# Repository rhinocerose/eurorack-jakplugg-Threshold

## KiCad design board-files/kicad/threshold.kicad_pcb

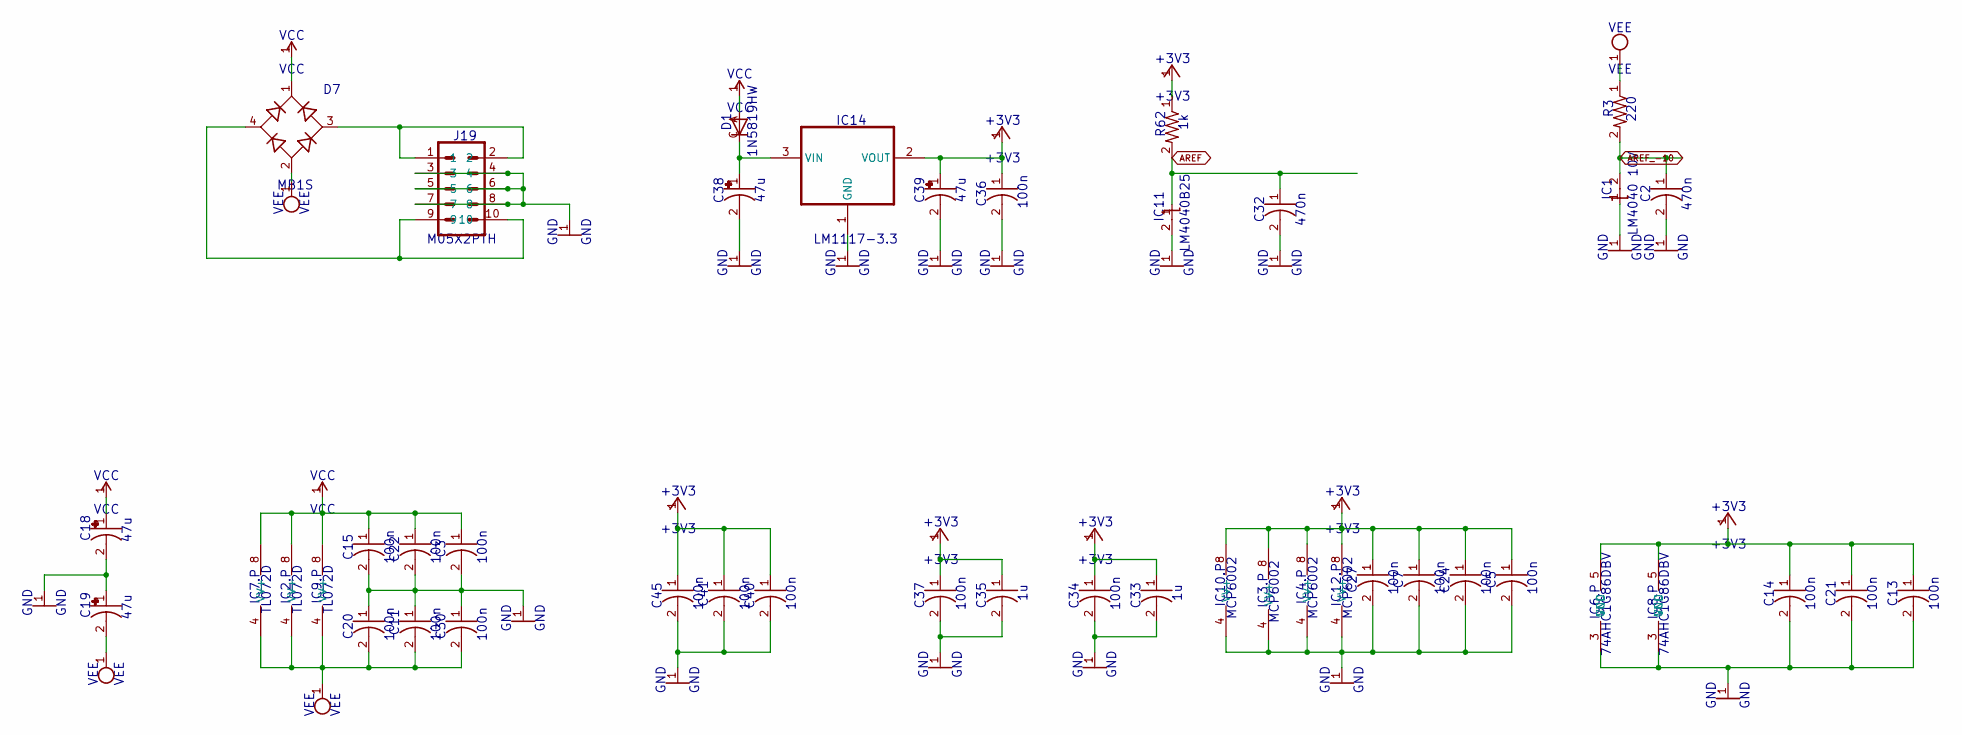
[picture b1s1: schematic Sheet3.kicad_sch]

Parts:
C2, C32: 470n; CAP_0603
C3, C5, C7, C11, C13, C14, C15, C20, C21, C22, C24, C27, C30, C34, C36, C37, C40, C41, C45: 100n; CAP_0603
C18, C19, C38, C39: 47u; CAPAE-5.3X5.3H7
C33, C35: 1u; CAP_0603
D1: 1N5819HW; SOD123
D7: MB1S; SOP-4_6.5X2.54
IC1: LM4040 10V; SOT23
IC2, IC7, IC9: TL072D; SO08_23
IC3, IC4, IC10, IC12: MCP6002; SO08_23
IC6, IC8: 74AHC1G86DBV; SOT23-5
IC11: LM4040B25; SOT23
IC14: LM1117-3.3; SOT223
J19: M05X2PTH; AVR_ICSP
R3: 220; RES_0603
R62: 1k; RES_0603

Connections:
+3V3: C5.1, C7.1, C13.1, C14.1, C21.1, C24.1, C27.1, C33.1, C34.1, C35.1, C36.1, C37.1, C39.1 (+), C40.1, C41.1, C45.1, IC3.8 (V+), IC4.8 (V+), IC6.5 (VCC), IC8.5 (VCC), IC10.8 (V+), IC12.8 (V+), IC14.2 (VOUT), R62.1; also elsewhere on the board
AREF: C32.1, IC11.1 (C), R62.2; also elsewhere on the board
AREF_-10: C2.1, IC1.2 (A), R3.2; also elsewhere on the board
GND: C2.2, C3.2, C5.2, C7.2, C11.1, C13.2, C14.2, C15.2, C18.2 (-), C19.1 (+), C20.1, C21.2, C22.2, C24.2, C27.2, C30.1, C32.2, C33.2, C34.2, C35.2, C36.2, C37.2, C38.2 (-), C39.2 (-), C40.2, C41.2, C45.2, IC1.1 (C), IC3.4 (V-), IC4.4 (V-), IC6.3 (GND), IC8.3 (GND), IC10.4 (V-), IC11.2 (A), IC12.4 (V-), IC14.1 (GND), J19.3, J19.4, J19.5, J19.6, J19.7, J19.8; also elsewhere on the board
unnamed: C38.1 (+), D1.C, IC14.3 (VIN)
Net_101: D7.3 (AC2), J19.1, J19.2
Net_139: D7.4 (AC1), J19.9, J19.10
VCC: C3.1, C15.1, C18.1 (+), C22.1, D1.A, D7.1 (+), IC2.8 (V+), IC7.8 (V+), IC9.8 (V+); also elsewhere on the board
VEE: C11.2, C19.2 (-), C20.2, C30.2, D7.2 (-), IC2.4 (V-), IC7.4 (V-), IC9.4 (V-), R3.1; also elsewhere on the board

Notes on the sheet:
100n
VEE
VCC
IC8.P
IC3.P
C19
GND
C35
C20
IC12.P
IC11
C22
+3V3
C21
C34
220
IC1
47u
C32
C11
C41
C24
C30
C15
LM1117-3.3
470n
1N5819HW
IC2.P
LM4040 10V
J19
LM4040B25
MCP6002
IC7.P
M05X2PTH
R62
TL072D
C40
C39
IC4.P
C14

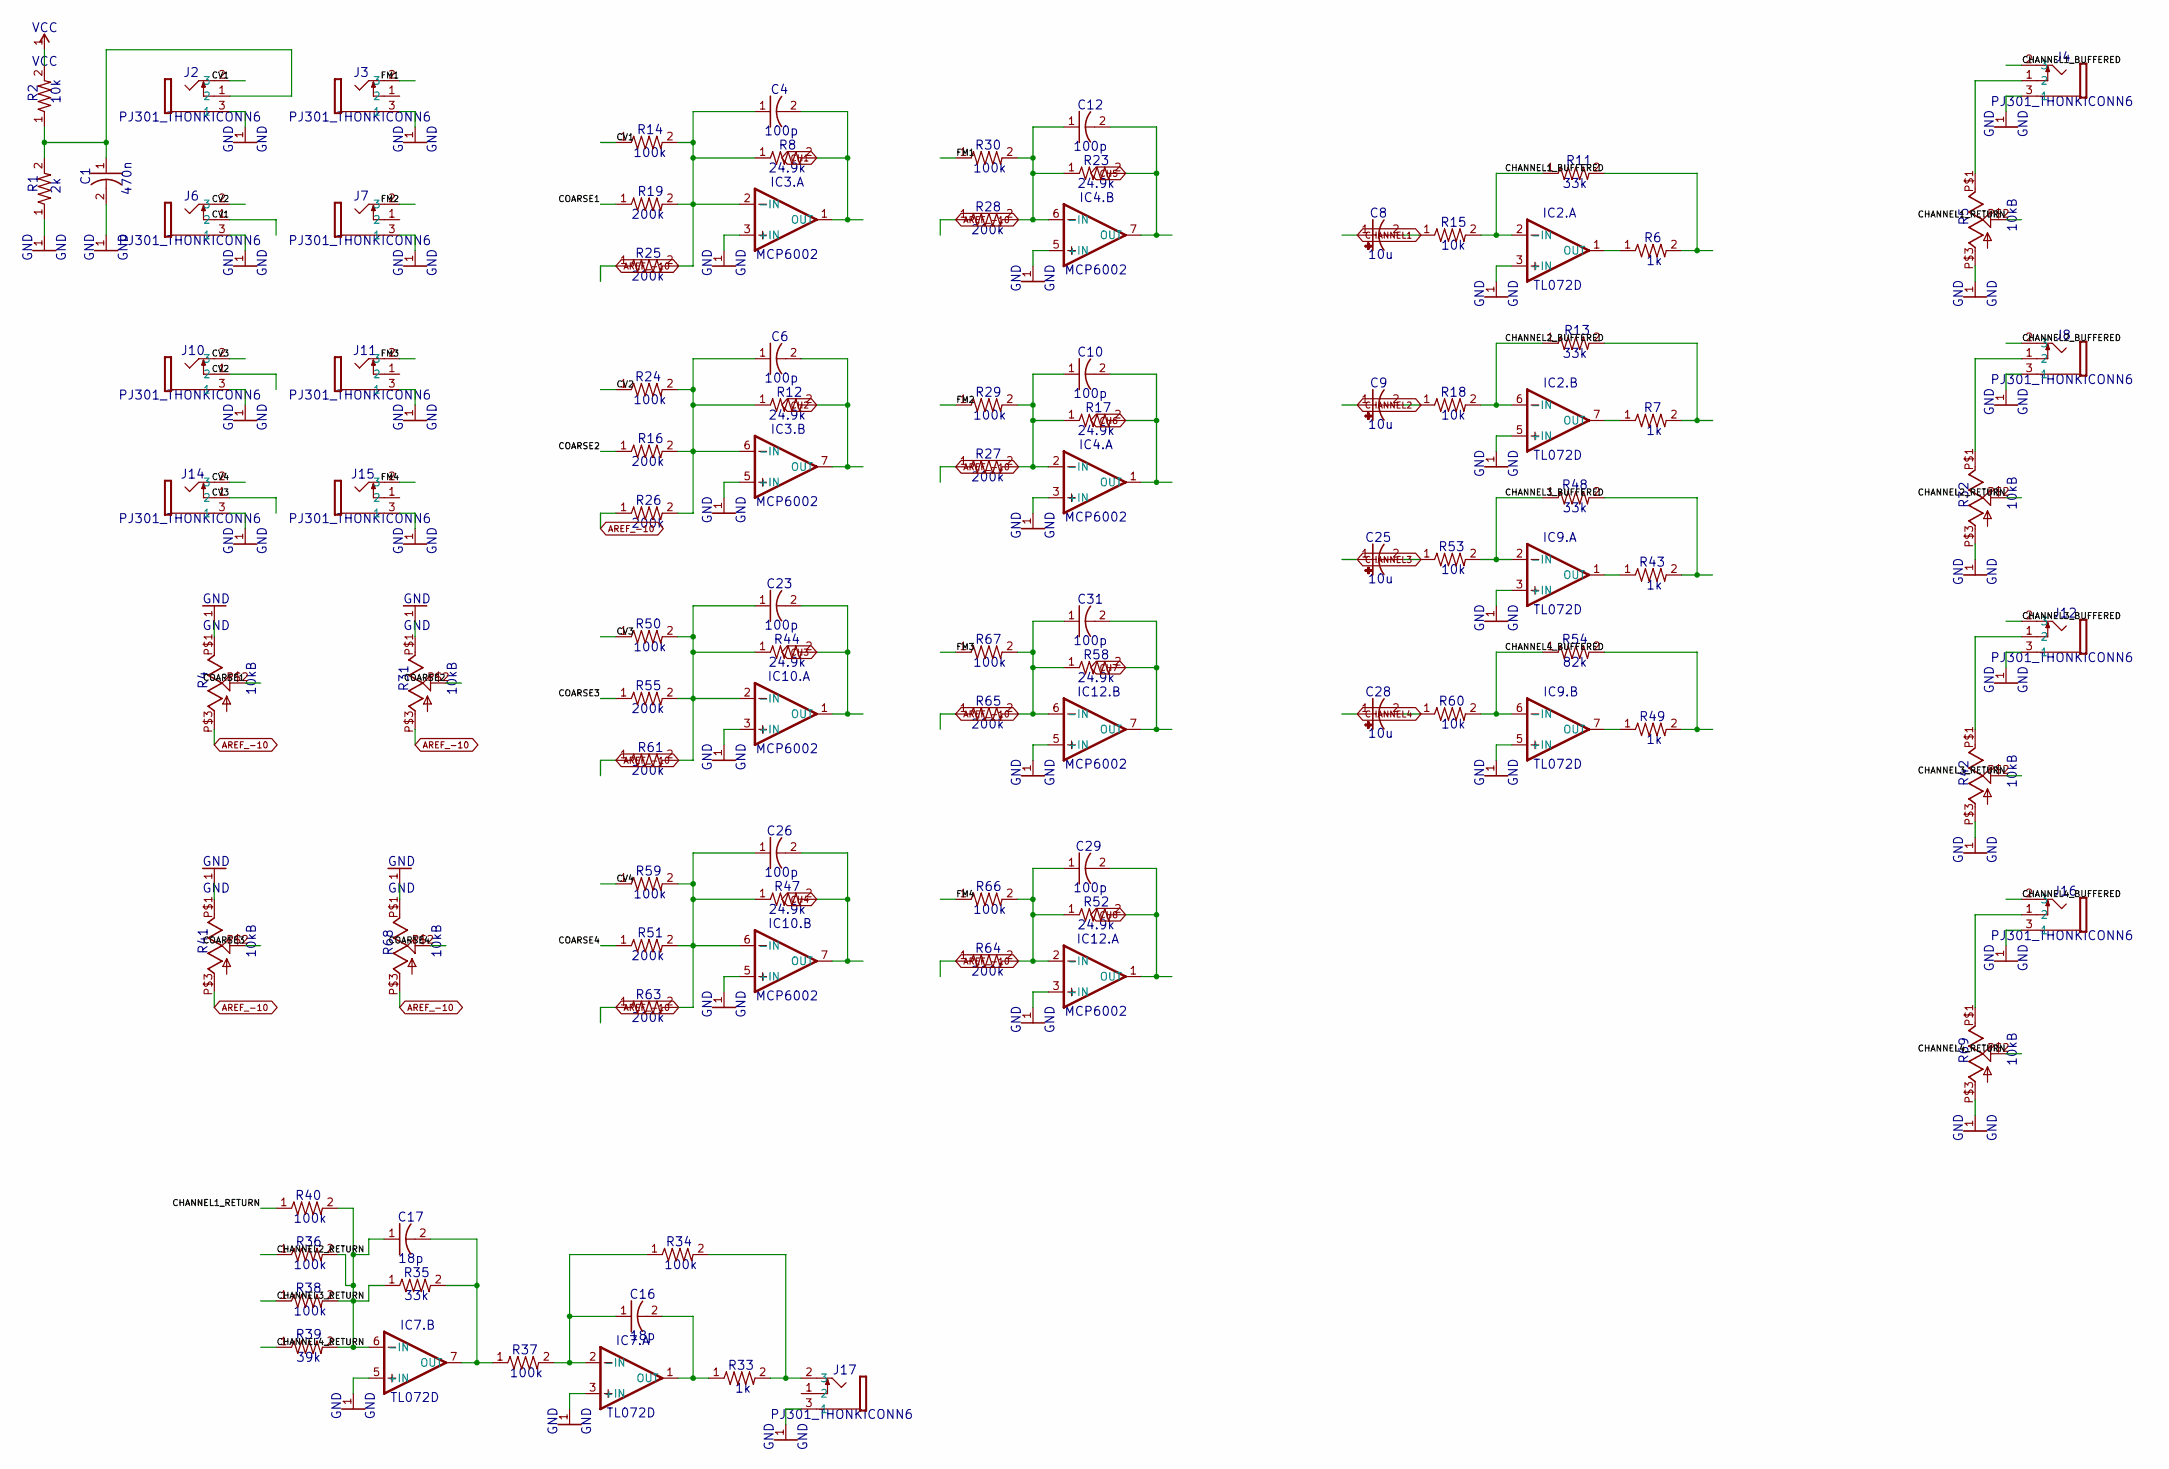
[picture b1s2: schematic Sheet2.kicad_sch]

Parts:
C1: 470n; CAP_0603
C4, C6, C10, C12, C23, C26, C29, C31: 100p; CAP_0603
C8, C9, C25, C28: 10u; CAP_1206
C16, C17: 18p; CAP_0603
IC2, IC7, IC9: TL072D; SO08_23
IC3, IC4, IC10, IC12: MCP6002; SO08_23
J2, J3, J4, J6, J7, J8, J10, J11, J12, J14, J15, J16, J17: PJ301_THONKICONN6; THONKICONN
R1: 2k; RES_0603
R2, R15, R18, R53, R60: 10k; RES_0603
R4, R5, R31, R32, R41, R42, R68, R69: 10kB; ALPS_POT_VERTICAL_PS
R6, R7, R33, R43, R49: 1k; RES_0603
R8, R12, R17, R23, R44, R47, R52, R58: 24.9k; RES_0603
R11, R13, R35, R48: 33k; RES_0603
R14, R24, R29, R30, R34, R36, R37, R38, R40, R50, R59, R66, R67: 100k; RES_0603
R16, R19, R25, R26, R27, R28, R51, R55, R61, R63, R64, R65: 200k; RES_0603
R39: 39k; RES_0603
R54: 82k; RES_0603

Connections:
AREF_-10: R4.P$3 (A), R25.1, R26.1, R27.1, R28.1, R31.P$3 (A), R41.P$3 (A), R61.1, R63.1, R64.1, R65.1, R68.P$3 (A); also elsewhere on the board
CH1: C4.2, IC3.1 (OUT), R8.2; also elsewhere on the board
CH2: C6.2, IC3.7 (OUT), R12.2; also elsewhere on the board
CH3: C23.2, IC10.1 (OUT), R44.2; also elsewhere on the board
CH4: C26.2, IC10.7 (OUT), R47.2; also elsewhere on the board
CH5: C12.2, IC4.7 (OUT), R23.2; also elsewhere on the board
CH6: C10.2, IC4.1 (OUT), R17.2; also elsewhere on the board
CH7: C31.2, IC12.7 (OUT), R58.2; also elsewhere on the board
CH8: C29.2, IC12.1 (OUT), R52.2; also elsewhere on the board
CHANNEL1: C8.1 (+); also elsewhere on the board
CHANNEL1_BUFFERED: J4.2 (3), R6.2, R11.2
CHANNEL1_RETURN: R5.P$2 (S), R40.1
CHANNEL2: C9.1 (+); also elsewhere on the board
CHANNEL2_BUFFERED: J8.2 (3), R7.2, R13.2
CHANNEL2_RETURN: R32.P$2 (S), R36.1
CHANNEL3: C25.1 (+); also elsewhere on the board
CHANNEL3_BUFFERED: J12.2 (3), R43.2, R48.2
CHANNEL3_RETURN: R38.1, R42.P$2 (S)
CHANNEL4: C28.1 (+); also elsewhere on the board
CHANNEL4_BUFFERED: J16.2 (3), R49.2, R54.2
CHANNEL4_RETURN: R39.1, R69.P$2 (S)
COARSE1: R4.P$2 (S), R19.1
COARSE2: R16.1, R31.P$2 (S)
COARSE3: R41.P$2 (S), R55.1
COARSE4: R51.1, R68.P$2 (S)
CV1: J2.2 (3), J6.1 (2), R14.1
CV2: J6.2 (3), J10.1 (2), R24.1
CV3: J10.2 (3), J14.1 (2), R50.1
CV4: J14.2 (3), R59.1
FM1: J3.2 (3), R30.1
FM2: J7.2 (3), R29.1
FM3: J11.2 (3), R67.1
FM4: J15.2 (3), R66.1
GND: C1.2, IC2.3 (+IN), IC2.5 (+IN), IC3.3 (+IN), IC3.5 (+IN), IC4.3 (+IN), IC4.5 (+IN), IC7.3 (+IN), IC7.5 (+IN), IC9.3 (+IN), IC9.5 (+IN), IC10.3 (+IN), IC10.5 (+IN), IC12.3 (+IN), IC12.5 (+IN), J2.3 (1), J3.3 (1), J4.3 (1), J6.3 (1), J7.3 (1), J8.3 (1), J10.3 (1), J11.3 (1), J12.3 (1), J14.3 (1), J15.3 (1), J16.3 (1), J17.3 (1), R1.1, R4.P$1 (E), R4.P$4, R4.P$5, R5.P$3 (A), R5.P$4, R5.P$5, R31.P$1 (E), R31.P$4, R31.P$5, R32.P$3 (A), R32.P$4, R32.P$5, R41.P$1 (E), R41.P$4, R41.P$5, R42.P$3 (A), R42.P$4, R42.P$5, R68.P$1 (E), R68.P$4, R68.P$5, R69.P$3 (A), R69.P$4, R69.P$5; also elsewhere on the board
MIX: J17.2 (3), R33.2, R34.2
unnamed: J8.1 (2), R32.P$1 (E)
unnamed: C23.1, IC10.2 (-IN), R44.1, R50.2, R55.2, R61.2
unnamed: C10.1, IC4.2 (-IN), R17.1, R27.2, R29.2
unnamed: C26.1, IC10.6 (-IN), R47.1, R51.2, R59.2, R63.2
unnamed: C31.1, IC12.6 (-IN), R58.1, R65.2, R67.2
unnamed: C29.1, IC12.2 (-IN), R52.1, R64.2, R66.2
unnamed: C8.2 (-), R15.1
unnamed: IC2.2 (-IN), R11.1, R15.2
unnamed: IC2.1 (OUT), R6.1
unnamed: C9.2 (-), R18.1
unnamed: IC2.6 (-IN), R13.1, R18.2
unnamed: IC2.7 (OUT), R7.1
unnamed: C25.2 (-), R53.1
unnamed: C12.1, IC4.6 (-IN), R23.1, R28.2, R30.2
unnamed: IC9.2 (-IN), R48.1, R53.2
unnamed: IC9.1 (OUT), R43.1
unnamed: C28.2 (-), R60.1
unnamed: IC9.6 (-IN), R54.1, R60.2
unnamed: IC9.7 (OUT), R49.1
unnamed: C17.1, IC7.6 (-IN), R35.1, R36.2, R38.2, R39.2, R40.2
unnamed: C16.1, IC7.2 (-IN), R34.1, R37.2
unnamed: C16.2, IC7.1 (OUT), R33.1
unnamed: J4.1 (2), R5.P$1 (E)
unnamed: C17.2, IC7.7 (OUT), R35.2, R37.1
unnamed: J12.1 (2), R42.P$1 (E)
unnamed: J16.1 (2), R69.P$1 (E)
unnamed: C6.1, IC3.6 (-IN), R12.1, R16.2, R24.2, R26.2
unnamed: C1.1, J2.1 (2), R1.2, R2.1
unnamed: C4.1, IC3.2 (-IN), R8.1, R14.2, R19.2, R25.2
VCC: R2.2; also elsewhere on the board

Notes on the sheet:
GND
PJ301_THONKICONN6
R50
TL072D
100k
R39
24.9k
100p
R69
R24
R48
R38
J15
J10
200k
470n
R63
R13
R43
R61
R52
10k
10u
MCP6002
R11
33k
C26
10kB
R28
R31
J11
R66
R65
R12
R49
IC7.B
IC2.B
R37
J17
IC12.B

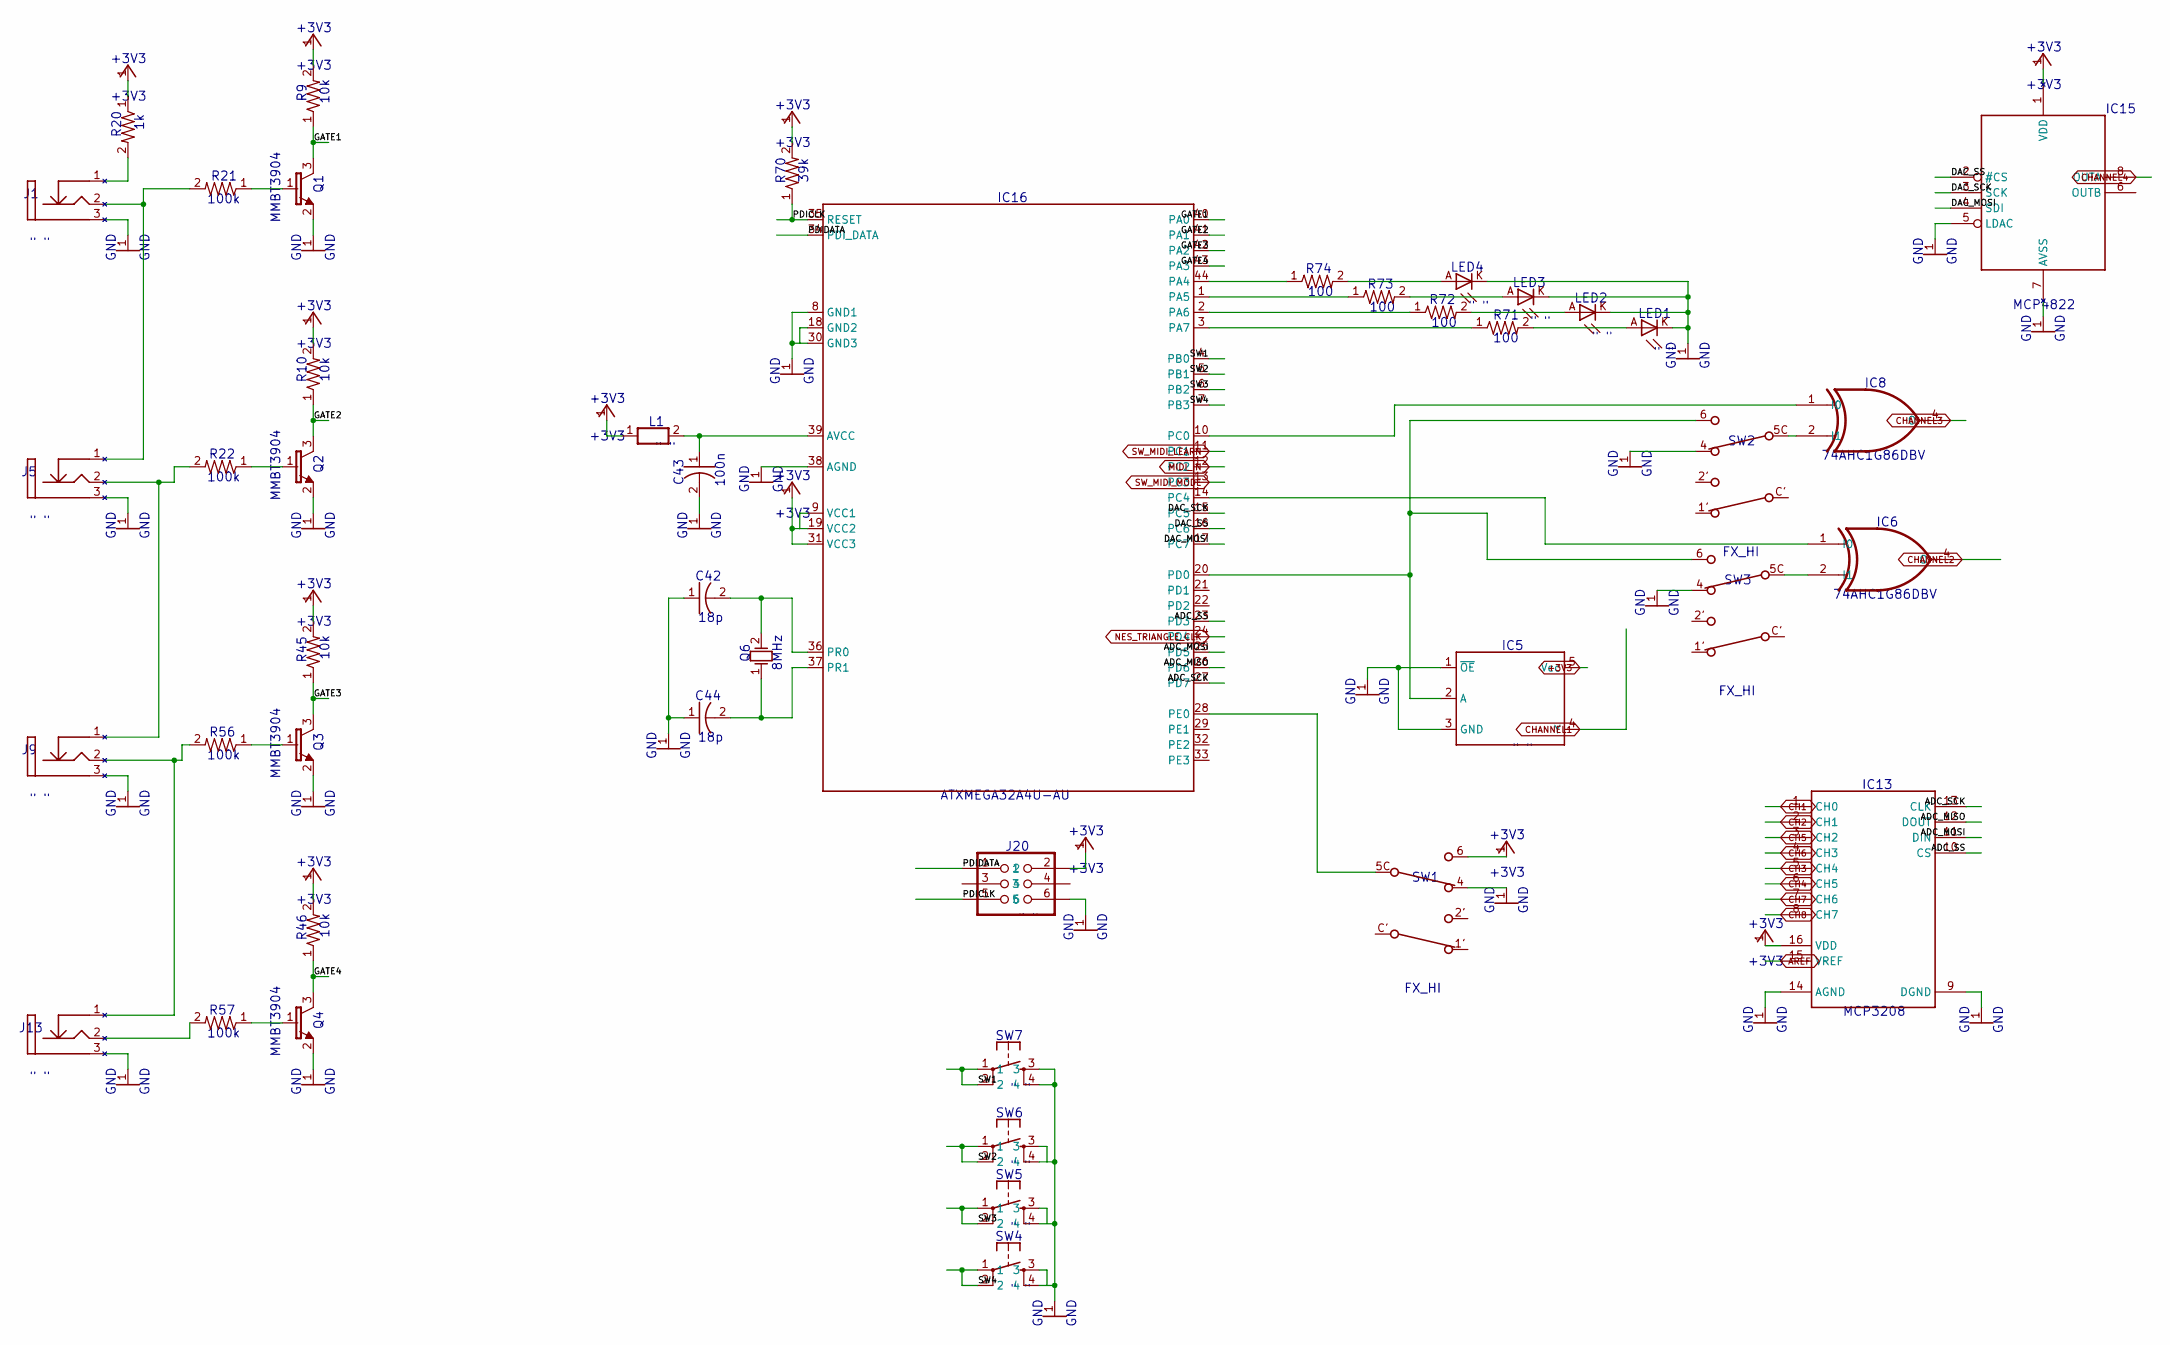
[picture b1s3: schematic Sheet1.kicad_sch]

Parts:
C42, C44: 18p; CAP_0603
C43: 100n; CAP_0603
IC5: 74AHC1G125GV; SOT23-5
IC6, IC8: 74AHC1G86DBV; SOT23-5
IC13: MCP3208; SO16
IC15: MCP4822; SO08
IC16: ATXMEGA32A4U-AU; TQFP44
J1, J5, J9, J13: THONKICONN; THONKICONN_JACK
J20: AVR_SPI_PRG_6PTH; 2X3
L1: WE-CBF_0603; 0603
LED1, LED2, LED3, LED4: LED3MM
Q1, Q2, Q3, Q4: MMBT3904; SOT23
Q6: 8MHz; TSC_7A_CRYSTAL
R9, R10, R45, R46: 10k; RES_0603
R20: 1k; RES_0603
R21, R22, R56, R57: 100k; RES_0603
R70: 39k; RES_0603
R71, R72, R73, R74: 100; RES_0603
SW1, SW2, SW3: FX_HI; PVB6I
SW4, SW5, SW6, SW7: TAC_SWITCHPTH; TACTILE-PTH

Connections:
+3V3: IC5.5 (Vcc), IC13.16 (VDD), IC15.1 (VDD), IC16.9 (VCC1), IC16.19 (VCC2), IC16.31 (VCC3), J20.2, L1.1, R9.2, R10.2, R20.1, R45.2, R46.2, R70.2, SW1.6 (C2@2); also elsewhere on the board
ADC_MISO: IC13.12 (DOUT), IC16.26 (PD6)
ADC_MOSI: IC13.11 (DIN), IC16.25 (PD5)
ADC_SCK: IC13.13 (CLK), IC16.27 (PD7)
ADC_SS: IC13.10 (CS), IC16.23 (PD3)
AREF: IC13.15 (VREF); also elsewhere on the board
CH1: IC13.1 (CH0); also elsewhere on the board
CH2: IC13.2 (CH1); also elsewhere on the board
CH3: IC13.5 (CH4); also elsewhere on the board
CH4: IC13.6 (CH5); also elsewhere on the board
CH5: IC13.3 (CH2); also elsewhere on the board
CH6: IC13.4 (CH3); also elsewhere on the board
CH7: IC13.7 (CH6); also elsewhere on the board
CH8: IC13.8 (CH7); also elsewhere on the board
CHANNEL1: IC5.4 (Y); also elsewhere on the board
CHANNEL2: IC6.4 (O); also elsewhere on the board
CHANNEL3: IC8.4 (O); also elsewhere on the board
CHANNEL4: IC15.8 (OUTA); also elsewhere on the board
DAC_MOSI: IC15.4 (SDI), IC16.17 (PC7)
DAC_SCK: IC15.3 (SCK), IC16.15 (PC5)
DAC_SS: IC15.2 (#CS), IC16.16 (PC6)
GATE1: IC16.40 (PA0), Q1.3 (C), R9.1
GATE1_IN: J1.2 (Tip), J5.1 (TN), R21.2
GATE1_LED: LED4.A, R74.2
GATE2: IC16.41 (PA1), Q2.3 (C), R10.1
GATE2_IN: J5.2 (Tip), J9.1 (TN), R22.2
GATE2_LED: LED3.A, R73.2
GATE3: IC16.42 (PA2), Q3.3 (C), R45.1
GATE3_IN: J9.2 (Tip), J13.1 (TN), R56.2
GATE3_LED: LED2.A, R72.2
GATE4: IC16.43 (PA3), Q4.3 (C), R46.1
GATE4_IN: J13.2 (Tip), R57.2
GATE4_LED: LED1.A, R71.2
GND: C42.1, C43.2, C44.1, IC5.1 (~OE), IC5.3 (GND), IC13.9 (DGND), IC13.14 (AGND), IC15.5 (LDAC), IC15.7 (AVSS), IC16.8 (GND1), IC16.18 (GND2), IC16.30 (GND3), IC16.38 (AGND), J1.3 (GND), J5.3 (GND), J9.3 (GND), J13.3 (GND), J20.6, LED1.K (C), LED2.K (C), LED3.K (C), LED4.K (C), Q1.2 (E), Q2.2 (E), Q3.2 (E), Q4.2 (E), SW1.3, SW1.4 (C3@2), SW2.3, SW2.4 (C3@2), SW3.3, SW3.4 (C3@2), SW4.3, SW4.4, SW5.3, SW5.4, SW6.3, SW6.4, SW7.3, SW7.4; also elsewhere on the board
MIDI_IN: IC16.12 (PC2); also elsewhere on the board
unnamed: Q1.1 (B), R21.1
unnamed: Q2.1 (B), R22.1
unnamed: Q3.1 (B), R56.1
unnamed: IC16.44 (PA4), R74.1
unnamed: IC16.1 (PA5), R73.1
unnamed: IC16.2 (PA6), R72.1
unnamed: IC16.3 (PA7), R71.1
unnamed: J1.1 (TN), R20.2
unnamed: IC6.1 (I0), IC16.14 (PC4)
unnamed: IC8.2 (I1), SW2.5C (C1@2)
unnamed: IC6.2 (I1), SW3.5C (C1@2)
unnamed: C43.1, IC16.39 (AVCC), L1.2
unnamed: IC8.1 (I0), IC16.10 (PC0)
unnamed: IC5.2 (A), IC16.20 (PD0), SW2.6 (C2@2), SW3.6 (C2@2)
unnamed: C44.2, IC16.37 (PR1), Q6.1 (OSC1)
unnamed: C42.2, IC16.36 (PR0), Q6.2 (OSC2)
unnamed: Q4.1 (B), R57.1
NES_TRIANGLE_CLK: IC16.24 (PD4); also elsewhere on the board
PDICLK: IC16.35 (RESET), J20.5, R70.1
PDIDATA: IC16.34 (PDI_DATA), J20.1
SW1: IC16.4 (PB0), SW7.1, SW7.2
SW2: IC16.5 (PB1), SW6.1, SW6.2
SW3: IC16.6 (PB2), SW5.1, SW5.2
SW4: IC16.7 (PB3), SW4.1, SW4.2
SW_MIDI_LEARN: IC16.11 (PC1); also elsewhere on the board
SW_MIDI_MODE: IC16.13 (PC3); also elsewhere on the board
SYNC_SWITCH: IC16.28 (PE0), SW1.5C (C1@2)

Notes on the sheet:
GND
R74
LED4
R45
LED3
MCP4822
R57
" "
FX_HI
+3V3
R22
SW2
74AHC1G86DBV
MMBT3904
SW4
10k
R20
MCP3208
R71
R46
IC8
SW1
C44
IC5
R72
C42
SW5
100
J13
R70
18p
39k
100k
R10
100n
8MHz
R56
SW3
J20
R21

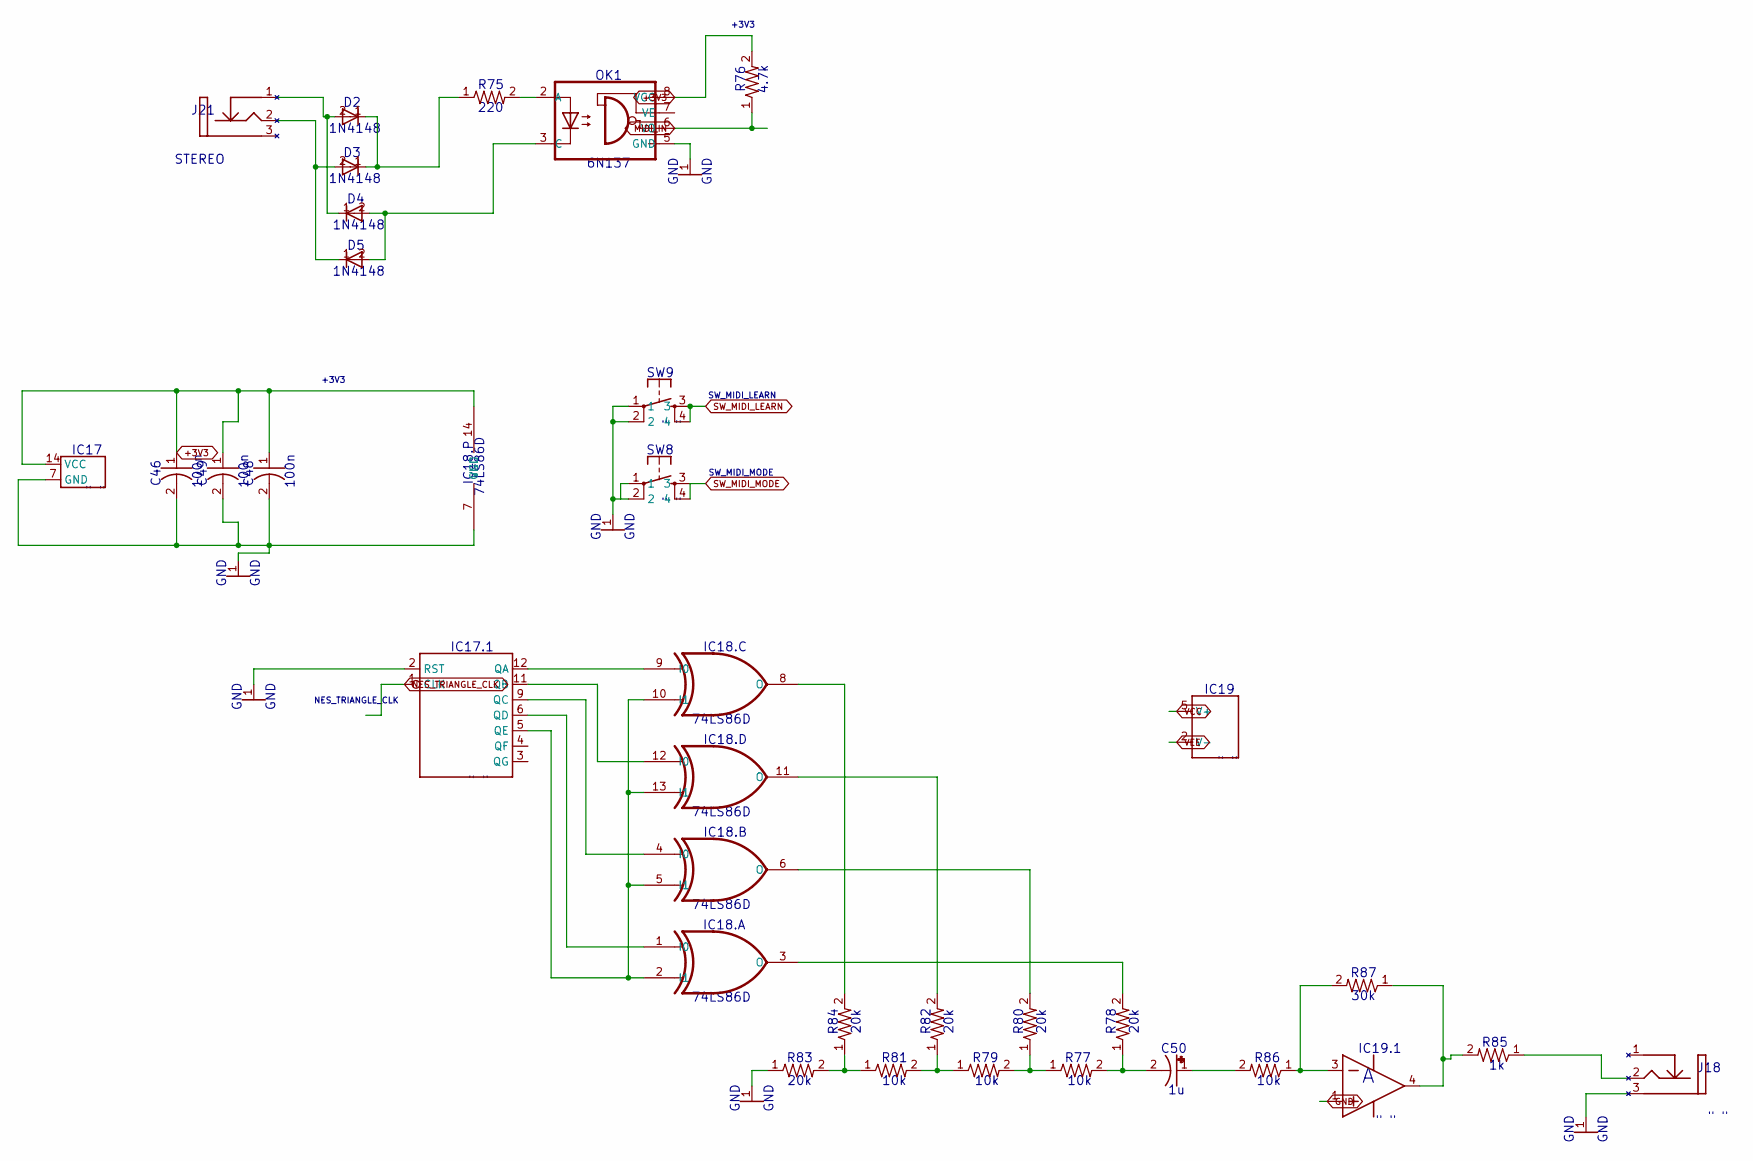
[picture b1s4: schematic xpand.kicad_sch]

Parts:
C46, C48, C49: 100n; CAP_0603
C50: 1u; CAP_0805
D2, D3, D4, D5: 1N4148; SOD-123F
IC17: M74HC4024M1R; SOIC-14_150MIL
IC18: 74LS86D; SOIC-14_150MIL
IC19: LM321MF; SOT23-5
J18: THONKICONN_35; THONKICONN_JACK
J21: STEREO; THONKICONN_JACK
OK1: 6N137; SOIC-8_150MIL
R75: 220; RES_0603
R76: 4.7k; RES_0603
R77, R79, R81, R86: 10k; RES_0603
R78, R80, R82, R83, R84: 20k; RES_0603
R85: 1k; RES_0603
R87: 30k; RES_0603
SW8, SW9: TAC_SWITCHPTH; TACTILE-PTH

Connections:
+3V3: C46.1, C48.1, C49.1, IC17.14 (VCC), IC18.14 (VCC), OK1.8 (VCC), R76.2; also elsewhere on the board
GND: C46.2, C48.2, C49.2, IC17.2 (RST), IC17.7 (GND), IC18.7 (GND), IC19.1 (IN+), J18.3 (GND), OK1.5 (GND), R83.1, SW8.1, SW8.2, SW9.1, SW9.2; also elsewhere on the board
MIDI_IN: OK1.6 (VO), R76.1; also elsewhere on the board
unnamed: IC17.5 (QE), IC18.2 (I1), IC18.5 (I1), IC18.10 (I1), IC18.13 (I1)
unnamed: IC17.11 (QB), IC18.12 (I0)
unnamed: IC17.12 (QA), IC18.9 (I0)
unnamed: IC17.6 (QD), IC18.1 (I0)
unnamed: R81.1, R83.2, R84.1
unnamed: R79.1, R81.2, R82.1
unnamed: R77.1, R79.2, R80.1
unnamed: C50.2 (-), R77.2, R78.1
unnamed: J18.2 (Tip), R85.1
NES_TRIANGLE_CLK: IC17.1 (CLK); also elsewhere on the board
Net_0: IC19.3 (IN-), R86.1, R87.2
Net_1: C50.1 (+), R86.2
Net_56: D4.2 (A), D5.2 (A), OK1.3 (C)
Net_57: D2.1 (C), D3.1 (C), R75.1
Net_113: D2.2 (A), D4.1 (C), J21.1 (TN)
Net_131: IC18.6 (O), R80.2
Net_132: IC18.3 (O), R78.2
Net_133: IC18.11 (O), R82.2
Net_134: IC18.8 (O), R84.2
Net_135: IC19.4 (OUT), R85.2, R87.1
Net_136: D3.2 (A), D5.1 (C), J21.2 (Tip)
Net_137: OK1.2 (A), R75.2
Net_138: IC17.9 (QC), IC18.4 (I0)
SW_MIDI_LEARN: SW9.3, SW9.4; also elsewhere on the board
SW_MIDI_MODE: SW8.3, SW8.4; also elsewhere on the board
VCC: IC19.5 (V+); also elsewhere on the board
VEE: IC19.2 (V-); also elsewhere on the board

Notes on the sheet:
220
10k
R82
R85
R76
6N137
" "
20k
R81
J21
SW_MIDI_MODE
GND
IC18.B
IC18.A
R79
OK1
R83
100n
+3V3
74LS86D
IC19
C50
IC17
IC18.P
IC19.1
IC18.C
J18
STEREO
R84
IC17.1
R87
R75
R80
IC18.D
R86
SW8
C48
NES_TRIANGLE_CLK
4.7k
C49

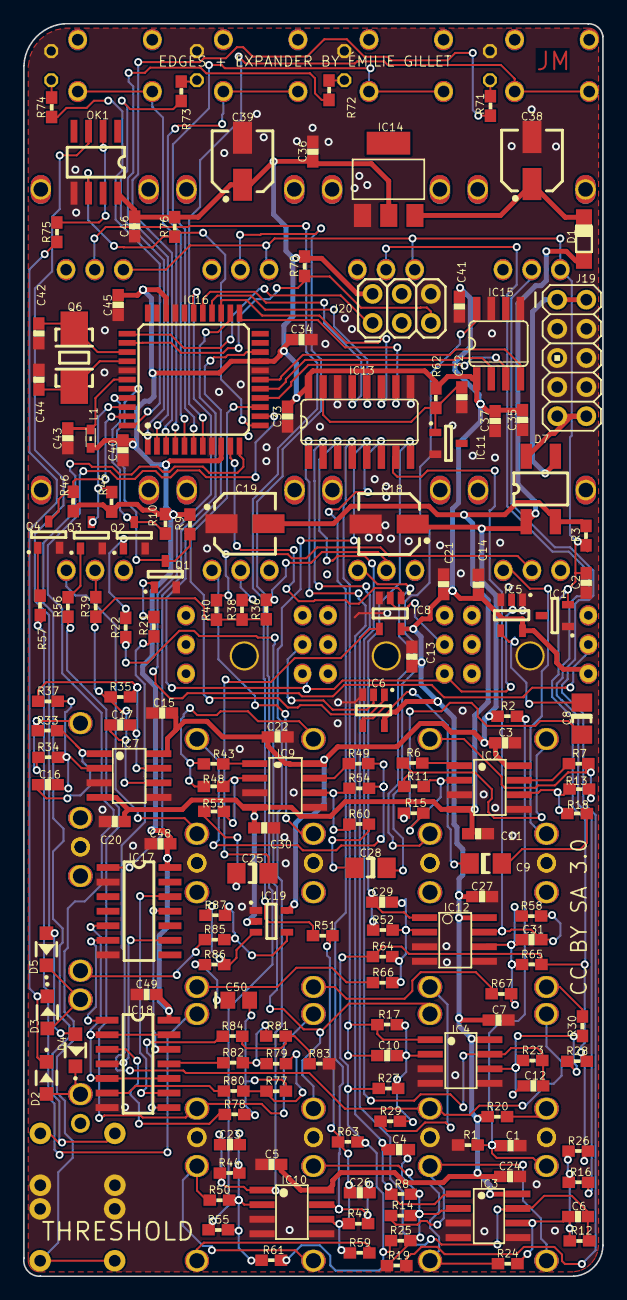
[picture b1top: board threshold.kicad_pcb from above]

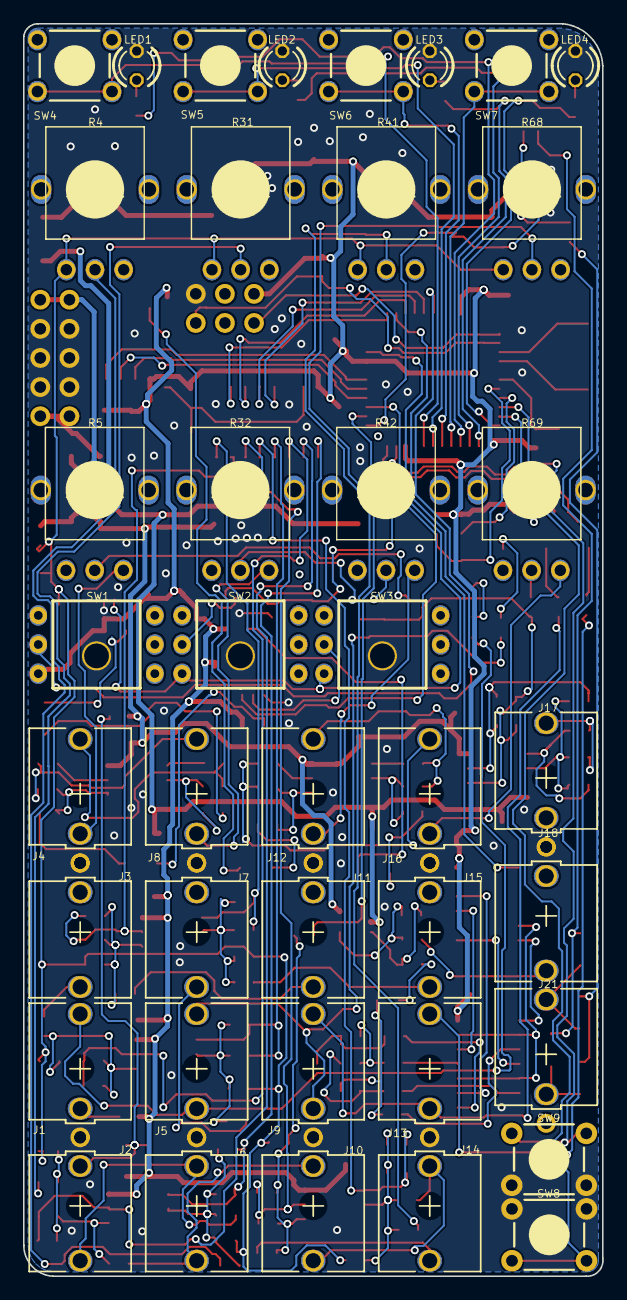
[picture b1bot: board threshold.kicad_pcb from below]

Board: 2 copper layers, 50.5 x 109.2 mm, 202 parts (40 on the bottom side), 140 nets.

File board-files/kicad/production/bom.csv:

Designator,Footprint,Quantity,Value,LCSC Part #
C1,CAP_0603,1,470n,
"C10, C23, C29, C4",CAP_0603_C4,4,100p,
C11,CAP_0603_C11,1,100n,
"C12, C26, C31, C6",CAP_0603,4,100p,
C13,CAP_0603_C13,1,100n,
"C14, C21",CAP_0603_C14,2,100n,
"C15, C37, C40",CAP_0603_C2,3,100n,
C16,CAP_0603_C4,1,18p,
C17,CAP_0603_C17,1,18p,
C18,CAPAE-5.3x5.3h7,1,47u,
C19,CAPAE-5.3x5.3h7_C19,1,47u,
C2,CAP_0603_C2,1,470n,
C20,CAP_0603_C20,1,100n,
"C22, C27, C3, C34, C7",CAP_0603,5,100n,
"C24, C36",CAP_0603_C17,2,100n,
"C25, C8",CAP_1206,2,10u,
C28,CAP_1206_C28,1,10u,
C30,CAP_0603_C30,1,100n,
C32,CAP_0603_C32,1,470n,
"C33, C35",CAP_0603_C2,2,1u,
"C38, C39",CAPAE-5.3x5.3h7_C38,2,47u,
C41,CAP_0603_C41,1,100n,
C42,CAP_0603_C42,1,18p,
"C43, C45, C5",CAP_0603_C4,3,100n,
C44,CAP_0603_C44,1,18p,
"C46, C48, C49",CAP_0603_C46,3,100n,
C50,CAP_0805,1,1u,
C9,CAP_1206_C9,1,10u,
D1,SOD123,1,1N5819HW,
D2,SOD-123F,1,1N4148,
D3,SOD-123F_D3,1,1N4148,
D4,SOD-123F_D4,1,1N4148,
D5,SOD-123F_D5,1,1N4148,
D7,SOP-4_6.5x2.54,1,MB1S,
IC1,SOT23,1,LM4040 10V,
"IC10, IC12, IC3, IC4",SO08,4,MCP6002,
IC11,SOT23_IC11,1,LM4040B25,
IC13,SO16,1,MCP3208,
IC14,SOT223,1,LM1117-3.3,
IC15,SO08_IC15,1,MCP4822,
IC16,TQFP44,1,ATXMEGA32A4U-AU,
IC17,SOIC-14_150mil,1,M74HC4024M1R,
IC18,SOIC-14_150mil,1,74LS86D,
IC19,SOT23-5_IC19,1,LM321MF,
"IC2, IC7, IC9",SO08,3,TL072D,
IC5,SOT23-5,1,74AHC1G125GV,
IC6,SOT23-5,1,74AHC1G86DBV,
IC8,SOT23-5_IC8,1,74AHC1G86DBV,
"J1, J9",Thonkiconn_Jack,2,THONKICONN,
"J10, J14",Thonkiconn_J10,2,PJ301_THONKICONN6,
"J11, J15, J3, J7",Thonkiconn_J3,4,PJ301_THONKICONN6,
"J12, J16, J4, J8",Thonkiconn_J4,4,PJ301_THONKICONN6,
"J13, J5",Thonkiconn_Jack_J5,2,THONKICONN,
J17,Thonkiconn_J17,1,PJ301_THONKICONN6,
J18,Thonkiconn_Jack_J18,1,THONKICONN,
J19,AVR_ICSP,1,M05X2PTH,
"J2, J6",Thonkiconn,2,PJ301_THONKICONN6,
J20,2X3,1,AVR_SPI_PRG_6PTH,
J21,Thonkiconn_Jack_J21,1,STEREO,
L1,0603,1,WE-CBF_0603,
"LED1, LED2, LED3, LED4",LED3MM,4,LED3MM,
OK1,SOIC-8_150mil,1,6N137,
Q1,SOT23_Q1,1,MMBT3904,
"Q2, Q3, Q4",SOT23_Q2,3,MMBT3904,
Q6,TSC_7A_crystal,1,8MHz,
R1,RES_0603,1,2k,
R10,RES_0603_R10,1,10k,
"R11, R48",RES_0603_R3,2,33k,
"R12, R23, R47, R58",RES_0603_R7,4,24.9k,
R13,RES_0603_R13,1,33k,
"R14, R29, R37, R50, R66",RES_0603_R7,5,100k,
"R15, R53",RES_0603_R7,2,10k,
"R16, R28, R65",RES_0603_R3,3,200k,
"R17, R44, R52, R8",RES_0603_R3,4,24.9k,
"R18, R60",RES_0603_R3,2,10k,
"R19, R26, R61, R63",RES_0603_R2,4,200k,
"R2, R86",RES_0603_R2,2,10k,
R20,RES_0603,1,1k,
"R21, R22, R30, R34, R36, R38, R40, R56, R59",RES_0603_R3,9,100k,
"R24, R67",RES_0603,2,100k,
"R25, R27, R55, R64",RES_0603_R7,4,200k,
R3,RES_0603_R3,1,300,
"R31, R32, R4, R41, R42, R5, R68, R69",ALPS_POT_VERTICAL_PS,8,10kB,
"R33, R6",RES_0603_R3,2,1k,
R35,RES_0603,1,33k,
R39,RES_0603_R3,1,39k,
R43,RES_0603_R43,1,1k,
"R45, R46",RES_0603_R45,2,10k,
"R49, R7",RES_0603_R7,2,1k,
R51,RES_0603,1,200k,
R54,RES_0603_R7,1,82k,
R57,RES_0603_R57,1,100k,
R62,RES_0603_R62,1,1k,
R70,RES_0603,1,39k,
"R71, R74",RES_0603,2,100,
R72,RES_0603_R72,1,100,
R73,RES_0603_R73,1,100,
R75,RES_0603_R75,1,220,
R76,RES_0603_R75,1,4.7k,
"R77, R79",RES_0603_R75,2,10k,
"R78, R80, R82, R83, R84",RES_0603_R78,5,20k,
R81,RES_0603_R78,1,10k,
R85,RES_0603_R75,1,1k,
R87,RES_0603_R2,1,30k,
R9,RES_0603,1,10k,
SW1,pvb6i,1,FX_HI,
"SW2, SW3",pvb6i_SW2,2,FX_HI,
"SW4, SW5",TACTILE-PTH,2,TAC_SWITCHPTH,
"SW6, SW7",TACTILE-PTH_SW6,2,TAC_SWITCHPTH,
SW8,TACTILE-PTH_SW8,1,TAC_SWITCHPTH,
SW9,TACTILE-PTH_SW9,1,TAC_SWITCHPTH,

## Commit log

2025-08-07 Kicad

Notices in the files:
board-files/kicad/threshold.kicad_pcb:
CC BY SA 3.0
